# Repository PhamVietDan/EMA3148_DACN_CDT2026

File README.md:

# Đồ án chuyên ngành Cơ điện tử: Thiết kế chế tạo quadcopter và xây dựng thuật toán giữ độ cao, vị trí cho quadcopter trong môi trường khép kín

Kho lưu trữ (Repository) này chứa các tài liệu, mã nguồn và dữ liệu tính toán của dự án (bao gồm cả phiên bản phần cứng nền tảng `drone_stm32f405rgt6` và phiên bản nâng cấp `drone_stm32h743vit6`).

## 🎯 Nhiệm vụ đảm nhiệm

### 1. Tính toán tải trọng và lực nâng
Trước khi tiến hành lựa chọn linh kiện, hệ thống cần được tính toán kỹ lưỡng để đảm bảo khả năng bay ổn định:
- **Tối ưu tải trọng:** Xác định tổng trọng lượng dự kiến của hệ thống (khung S500, pin 5300mAh, vi điều khiển, cảm biến...).
- **Phân tích lực nâng:** Đánh giá và tính toán lực đẩy (Thrust) thực tế tạo ra từ cấu hình tổ hợp: Động cơ Phantom 3 850KV + Cánh quạt 9450 + Nguồn điện 14.8V (Pin 4S). 
- **Mục tiêu:** Đạt được tỷ lệ lực đẩy/trọng lượng (Thrust-to-Weight Ratio) tối ưu, nhằm đảm bảo drone cất cánh an toàn, bay ổn định và xác định được giới hạn tải trọng dư thừa nếu gắn thêm thiết bị (như camera, gimbal).

### 2. Lựa chọn linh kiện và Tích hợp phần cứng
Dựa trên các thông số tính toán lực nâng và tải trọng ở trên, hệ thống phần cứng được chốt cấu hình và tiến hành mua sắm, lắp ráp. Dưới đây là bảng chi tiết các module được sử dụng:

| Phân loại | Tên linh kiện | Chức năng chính | Hình ảnh minh họa |
| :--- | :--- | :--- | :---: |
| **Bộ điều khiển trung tâm** | **Kit WeAct STM32F405RGT6** *(Phiên bản 1)* | Vi điều khiển trung tâm (Flight Controller) giai đoạn đầu, xử lý thuật toán bay cơ bản. |  |
| | **Kit DevEBox STM32H743VIT6** *(Nâng cấp)* | Vi điều khiển trung tâm hiệu năng cao (480MHz), mở rộng tài nguyên tính toán. |  |
| **Cảm biến & Định vị** | **IMU BMI323** *(Phiên bản 1)* | Đo lường quán tính (gia tốc và góc quay) dùng trong giai đoạn đầu. |  |
| | **IMU ICM-42688** *(Nâng cấp)* | Thay thế BMI323 trên bo mạch SPIDER_H7_FC, giảm nhiễu và tăng độ chính xác. |  |
| | **Optical Flow MTF-01P** | Cảm biến quang học hỗ trợ giữ vị trí tầm thấp. |  |
| | **GPS GEP-M10-DI** | Module La bàn và định vị vệ tinh. |  |
| **Giao tiếp & Telemetry** | **Module ESP32-C3** | Truyền nhận dữ liệu Telemetry không dây theo thời gian thực (dùng từ phiên bản 1). | |
| **Hệ thống Động lực** | **Khung (Frame) S500** | Khung giá đỡ chịu lực cho toàn bộ hệ thống drone. | |
| | **Động cơ Phantom 3 850KV** | Động cơ không chổi than (Brushless Motor) tạo lực quay. | |
| | **Cánh quạt 9450** | Tạo lực nâng đẩy hệ thống khi kết hợp với động cơ. | |
| **Năng lượng & Giao tiếp** | **Pin LiPo Ovonic 4S 5300mAh** | Cấp nguồn năng lượng (14.8V) cho toàn bộ cấu hình. | |
| | **Bộ Tay điều khiển (Tx/Rx)** | Giao tiếp sóng RF để điều khiển drone từ xa. | |

### 3. Nâng cấp phần cứng & Thiết kế mạch in (PCB - SPIDER_H7_FC)
Để đáp ứng yêu cầu xử lý các thuật toán điều khiển phức tạp, giảm nhiễu dây cắm và tăng độ ổn định cơ khí, hệ thống được nâng cấp từ **STM32F405RGT6** (đấu nối dây rời) sang **STM32H743VIT6** tích hợp trên bo mạch chủ tự thiết kế **SPIDER_H7_FC**:

- **Lý do nâng cấp:** Tận dụng xung nhịp cao (480MHz) và tập lệnh DSP/FPU mạnh mẽ của dòng STM32H7 để chạy bộ lọc Kalman và vòng lặp điều khiển tần số cao mượt mà hơn, đồng thời khắc phục tình trạng lỏng dây tín hiệu khi drone rung động.
- **Đặc điểm thiết kế mạch SPIDER_H7_FC:**
  - **Tích hợp cảm biến & Telemetry:** Bố trí đế cắm trực tiếp cho cảm biến quán tính **ICM-42688** và module truyền dữ liệu không dây **ESP32-C3** (`TELEMETRY ESP C3`).
  - **Nguồn & Giám sát:** Hỗ trợ đầu vào nguồn pin 4S (`+16V`), đường nguồn ổn áp `+5V`, tích hợp mạch Op-amp `LMV358` đo điện áp pin và còi báo trạng thái (`BZ1`).

<div align="center">
  <table>
    <tr>
      <td align="center">
        <br>
        <sub><b>Mặt trên (Top Layer)</b></sub>
      </td>
      <td align="center">
        <br>
        <sub><b>Mặt dưới (Bottom Layer)</b></sub>
      </td>
    </tr>
    <tr>
      <td colspan="2" align="center">
        <br>
        <sub><b>Bo mạch SPIDER_H7_FC thực tế (bản nâng cấp)</b></sub>
      </td>
    </tr>
  </table>
</div>

### 4. Hình ảnh thực tế của Drone sau khi lắp ráp
<div align="center">
  <table>
    <tr>
      <td align="center">
        <br>
        <sub><b>Drone Ver 1 (STM32F405RGT6 - đấu nối dây rời)</b></sub>
      </td>
      <td align="center">
        <br>
        <sub><b>Drone Ver 2 (SPIDER_H7_FC - bản nâng cấp)</b></sub>
      </td>
    </tr>
  </table>
</div>

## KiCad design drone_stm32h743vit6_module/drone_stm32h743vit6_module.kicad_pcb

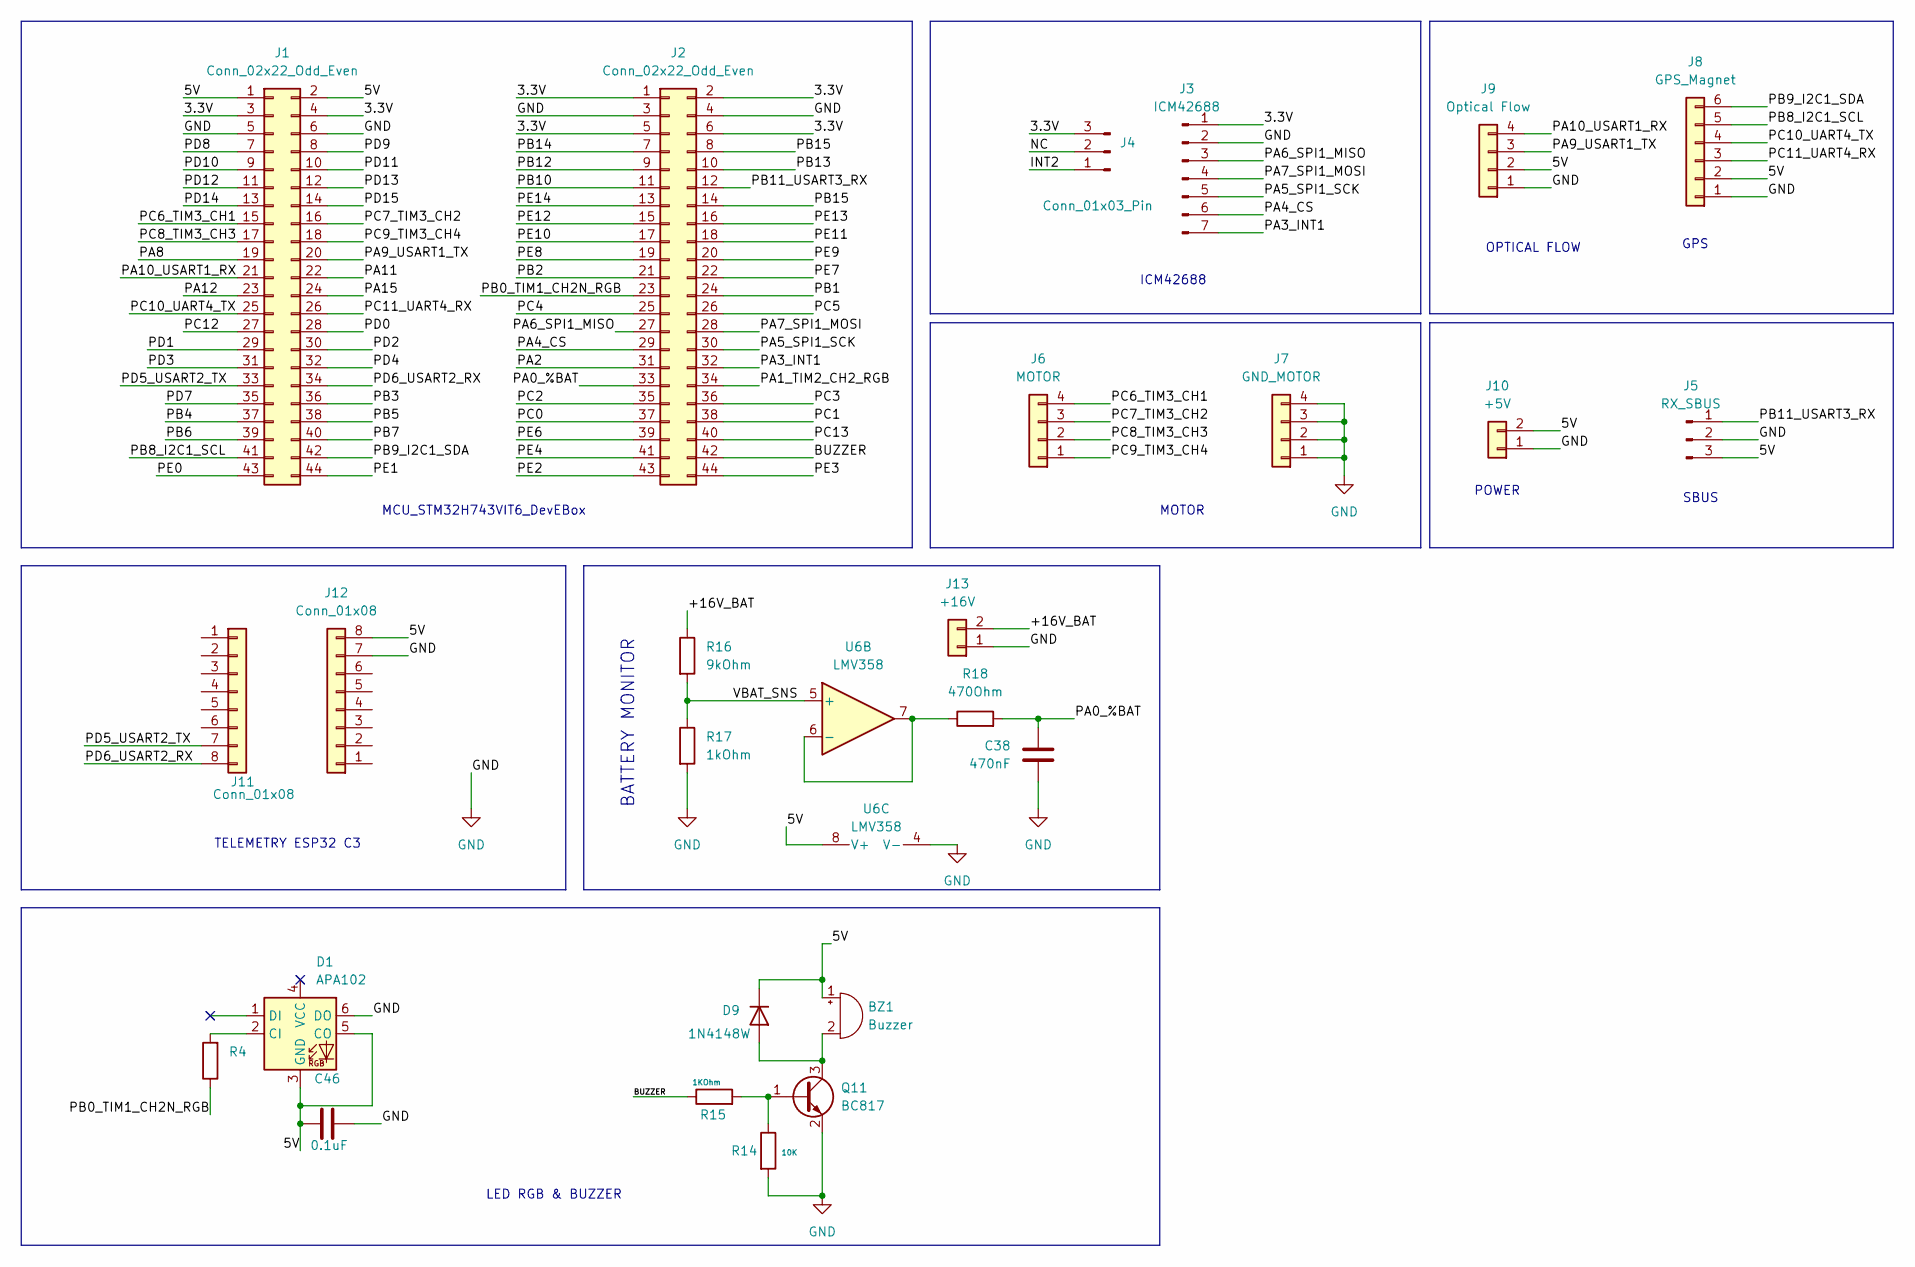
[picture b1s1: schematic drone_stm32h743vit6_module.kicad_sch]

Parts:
BZ1: Buzzer; Buzzer_12x9.5RM7.6
C38: 470nF; C_0603_1608Metric
C46: 0.1uF; C_0603_1608Metric
D1: APA102; LED_RGB_5050-6
D9: 1N4148W; D_SOD-123
J1, J2: Conn_02x22_Odd_Even; PinSocket_2x22_P2.54mm_Vertical
J3: ICM42688; PinSocket_1x07_P2.54mm_Vertical
J4: Conn_01x03_Pin; PinSocket_1x03_P2.54mm_Vertical
J5: RX_SBUS; JST_XH_S3B-XH-A-1_1x03_P2.50mm_Horizontal
J6: MOTOR; JST_XH_S4B-XH-A-1_1x04_P2.50mm_Horizontal
J7: GND_MOTOR; JST_XH_S4B-XH-A-1_1x04_P2.50mm_Horizontal
J8: GPS_Magnet; JST_XH_S6B-XH-A-1_1x06_P2.50mm_Horizontal
J9: Optical Flow; JST_XH_S4B-XH-A-1_1x04_P2.50mm_Horizontal
J10: +5V; JST_XH_S2B-XH-A-1_1x02_P2.50mm_Horizontal
J11, J12: Conn_01x08; PinSocket_1x08_P2.54mm_Vertical
J13: +16V; JST_XH_S2B-XH-A-1_1x02_P2.50mm_Horizontal
Q11: BC817; SOT-23
R4: 300Ohm; R_0805_2012Metric
R14: 10K; R_0603_1608Metric
R15: 1KOhm; R_0603_1608Metric
R16: 9kOhm; R_0603_1608Metric
R17: 1kOhm; R_0603_1608Metric
R18: 470Ohm; R_0603_1608Metric
U6: LMV358; SOIC-8_3.9x4.9mm_P1.27mm

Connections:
/3.3V: J1.3, J1.4, J2.1, J2.2, J2.5, J2.6, J3.1, J4.3
/5V: BZ1.1 (+), C46.1, D1.3 (GND), D1.5 (CO), D9.1 (K), J1.1, J1.2, J5.3, J8.2, J9.2, J10.2, J12.8, U6.8 (V+)
/+16V_BAT: J13.2, R16.1
/BUZZER: J2.42, R15.1
/INT2: J4.1
/NC: J4.2
/PA0_%BAT: C38.1, J2.33, R18.2
/PA1_TIM2_CH2_RGB: J2.34
/PA2: J2.31
/PA3_INT1: J2.32, J3.7
/PA4_CS: J2.29, J3.6
/PA5_SPI1_SCK: J2.30, J3.5
/PA6_SPI1_MISO: J2.27, J3.3
/PA7_SPI1_MOSI: J2.28, J3.4
/PA8: J1.19
/PA9_USART1_TX: J1.20, J9.3
/PA10_USART1_RX: J1.21, J9.4
/PA11: J1.22
/PA12: J1.23
/PA15: J1.24
/PB0_TIM1_CH2N_RGB: J2.23, R4.1
/PB1: J2.24
/PB2: J2.21
/PB3: J1.36
/PB4: J1.37
/PB5: J1.38
/PB6: J1.39
/PB7: J1.40
/PB8_I2C1_SCL: J1.41, J8.5
/PB9_I2C1_SDA: J1.42, J8.6
/PB10: J2.11
/PB11_USART3_RX: J2.12, J5.1
/PB12: J2.9
/PB13: J2.10
/PB14: J2.7
/PB15: J2.8, J2.14
/PC0: J2.37
/PC1: J2.38
/PC2: J2.35
/PC3: J2.36
/PC4: J2.25
/PC5: J2.26
/PC6_TIM3_CH1: J1.15, J6.4
/PC7_TIM3_CH2: J1.16, J6.3
/PC8_TIM3_CH3: J1.17, J6.2
/PC9_TIM3_CH4: J1.18, J6.1
/PC10_UART4_TX: J1.25, J8.4
/PC11_UART4_RX: J1.26, J8.3
/PC12: J1.27
/PC13: J2.40
/PD0: J1.28
/PD1: J1.29
/PD2: J1.30
/PD3: J1.31
/PD4: J1.32
/PD5_USART2_TX: J1.33, J11.7
/PD6_USART2_RX: J1.34, J11.8
/PD7: J1.35
/PD8: J1.7
/PD9: J1.8
/PD10: J1.9
/PD11: J1.10
/PD12: J1.11
/PD13: J1.12
/PD14: J1.13
/PD15: J1.14
/PE0: J1.43
/PE1: J1.44
/PE2: J2.43
/PE3: J2.44
/PE4: J2.41
/PE6: J2.39
/PE7: J2.22
/PE8: J2.19
/PE9: J2.20
/PE10: J2.17
/PE11: J2.18
/PE12: J2.15
/PE13: J2.16
/PE14: J2.13
/VBAT_SNS: R16.2, R17.1, U6.5 (+)
GND: C38.2, C46.2, D1.6 (DO), J1.5, J1.6, J2.3, J2.4, J3.2, J5.2, J7.1, J7.2, J7.3, J7.4, J8.1, J9.1, J10.1, J12.7, J13.1, Q11.2 (E), R14.2, R17.2, U6.4 (V-)
unnamed: BZ1.2 (-), D9.2 (A), Q11.3 (C)
unnamed: D1.2 (CI), R4.2
unnamed: Q11.1 (B), R14.1, R15.2
unnamed: R18.1, U6.6 (-), U6.7

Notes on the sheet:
OPTICAL FLOW
GPS
POWER
BATTERY MONITOR
MCU_STM32H743VIT6_DevEBox
TELEMETRY ESP32 C3
SBUS
MOTOR
ICM42688
LED RGB & BUZZER

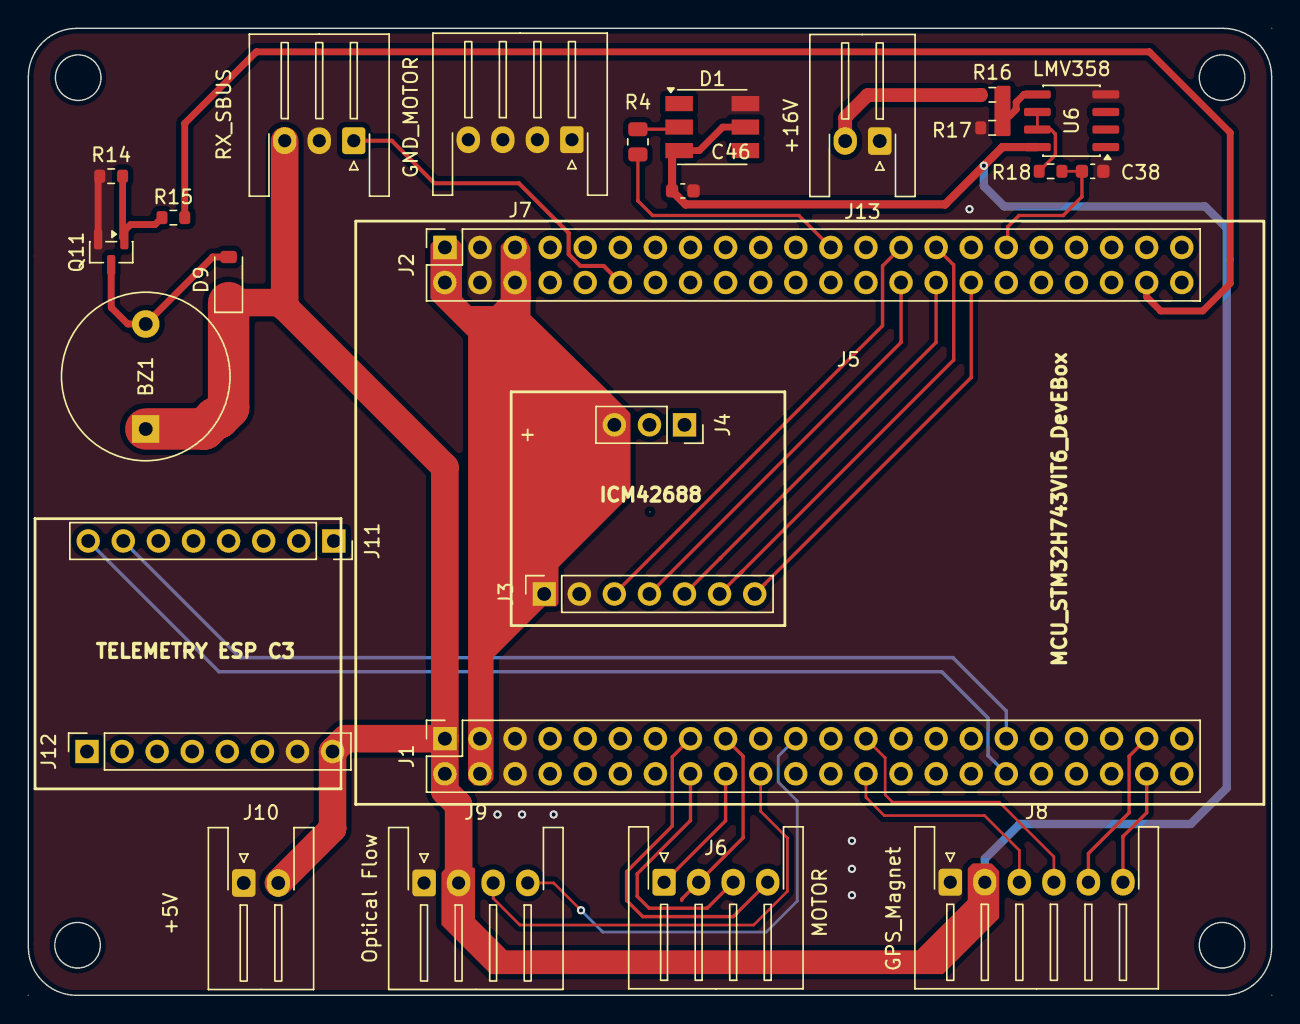
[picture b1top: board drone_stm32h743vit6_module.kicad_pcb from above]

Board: 2 copper layers, 90.0 x 70.0 mm, 26 parts (0 on the bottom side), 31 nets.
